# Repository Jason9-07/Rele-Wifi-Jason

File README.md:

Rele Wifi - ESP8266

  En este proyecto el ESP8266 se logro su funcionamiento. Tiene como propósito funcionar en proyectos de detección de temperatura en tanques de agua, con el finde asegurar de tener el recipiente lleno dependiendo de los datos que se le asigno, regular la temperatura y dar aviso de cualquier falla del funcionamiento como de falla de regulación de agua, sobre aumento de liquido o sustancia que contenga.

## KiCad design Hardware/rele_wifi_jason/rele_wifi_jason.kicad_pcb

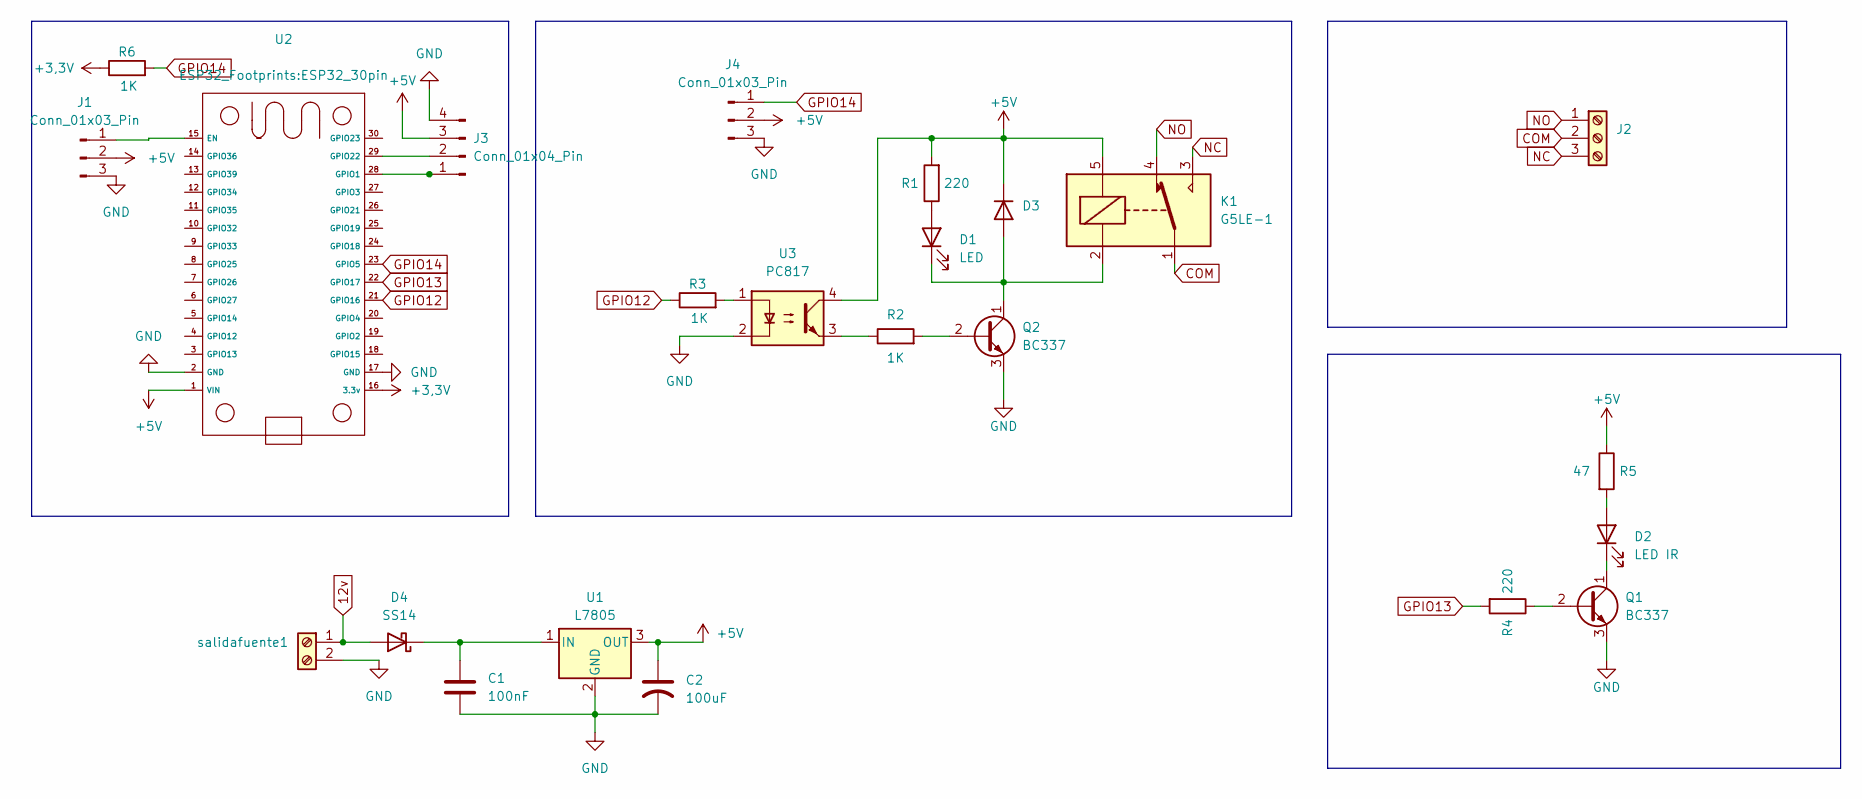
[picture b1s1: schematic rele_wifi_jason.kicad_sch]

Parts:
C1: 100nF; CP_Radial_D8.0mm_P5.00mm
C2: 100uF; CP_Radial_D8.0mm_P5.00mm
D1: LED; LED_D3.0mm_Clear
D2: LED IR; LED_D3.0mm_Clear
D3: 1N4007; D_DO-41_SOD81_P12.70mm_Horizontal
D4: SS14; D_5W_P10.16mm_Horizontal
J1, J4: Conn_01x03_Pin; TerminalBlock_bornier-3_P5.08mm
J2: Screw_Terminal_01x03; TerminalBlock_MaiXu_MX126-5.0-03P_1x03_P5.00mm
J3: Conn_01x04_Pin
K1: G5LE-1; Relay_SPDT_Omron-G5LE-1
Q1, Q2: BC337; TO-92_Inline
R1, R4: 220; R_0805_2012Metric
R2, R3: 1K; R_0805_2012Metric
R5: 47; R_0805_2012Metric
R6: 1K; R_Axial_DIN0207_L6.3mm_D2.5mm_P10.16mm_Horizontal
U1: L7805; TO-220-3_Vertical
U2: ESP32_30pin
U3: PC817; DIP-4_W7.62mm
salidafuente1: Screw_Terminal_01x02; TerminalBlock_bornier-2_P5.08mm

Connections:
12v: D4.2 (A), salidafuente1.1
+3,3V: R6.1, U2.16 (3.3v)
+5V: C2.1, D3.1 (K), J1.2, J3.3, J4.2, K1.5, R1.2, R5.1, U1.3 (OUT), U2.1 (VIN), U3.4
COM: J2.2, K1.1
GND: C1.2, C2.2, J1.3, J3.4, J4.3, Q1.3 (E), Q2.3 (E), U1.2 (GND), U2.2 (GND), U2.17 (GND), U3.2, salidafuente1.2
GPIO12: R3.1, U2.21 (GPIO16)
GPIO13: R4.2, U2.22 (GPIO17)
GPIO14: J4.1, R6.2, U2.23 (GPIO5)
NC: J2.3, K1.3
NO: J2.1, K1.4
unnamed: D1.2 (A), R1.1
unnamed: D1.1 (K), D3.2 (A), K1.2, Q2.1 (C)
unnamed: D2.2 (A), R5.2
unnamed: D2.1 (K), Q1.1 (C)
unnamed: C1.1, D4.1 (K), U1.1 (IN)
unnamed: J1.1, U2.15 (EN)
unnamed: J3.1, U2.28 (GPIO1)
unnamed: J3.2, U2.29 (GPIO22)
unnamed: Q1.2 (B), R4.1
unnamed: Q2.2 (B), R2.2
unnamed: R2.1, U3.3
unnamed: R3.2, U3.1

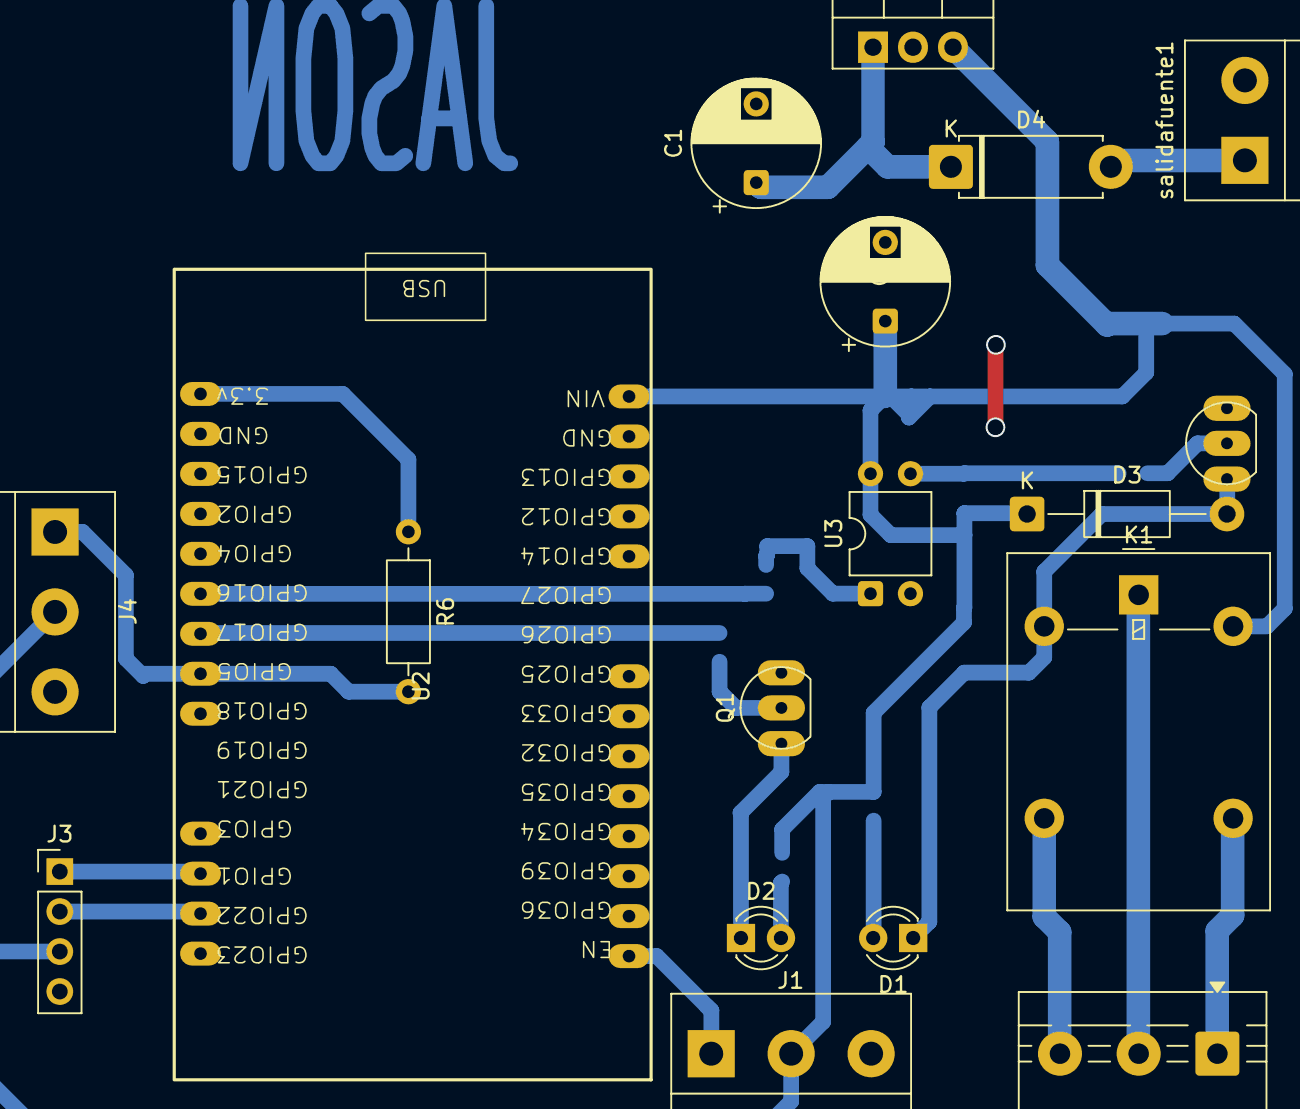
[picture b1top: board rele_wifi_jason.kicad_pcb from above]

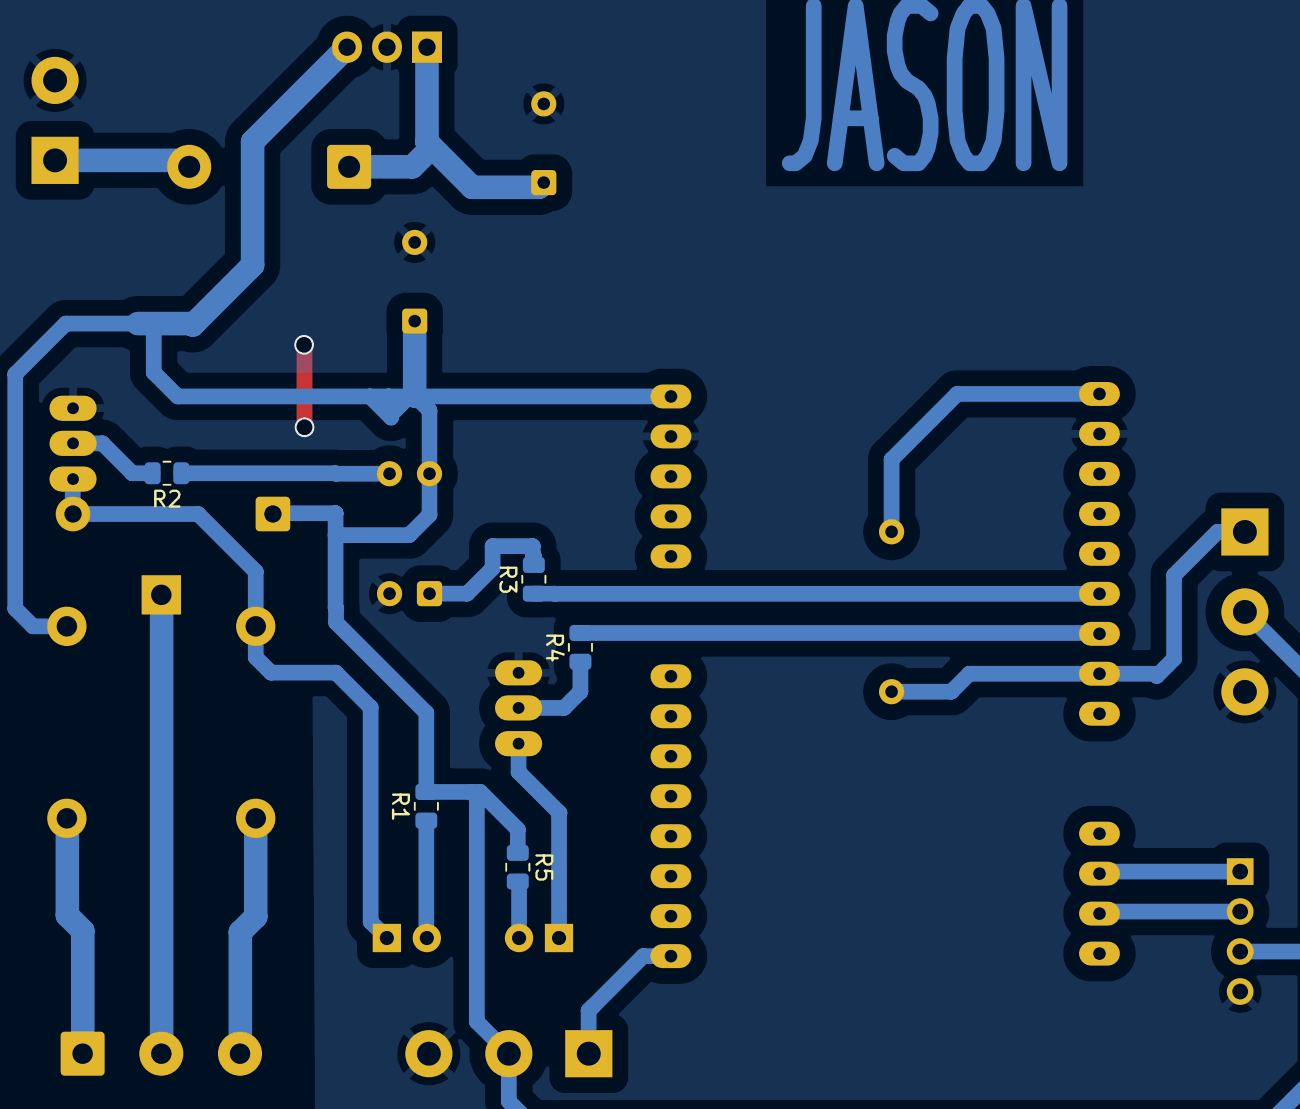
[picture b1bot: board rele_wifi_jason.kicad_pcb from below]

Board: 2 copper layers, 23 parts (5 on the bottom side), 22 nets.
